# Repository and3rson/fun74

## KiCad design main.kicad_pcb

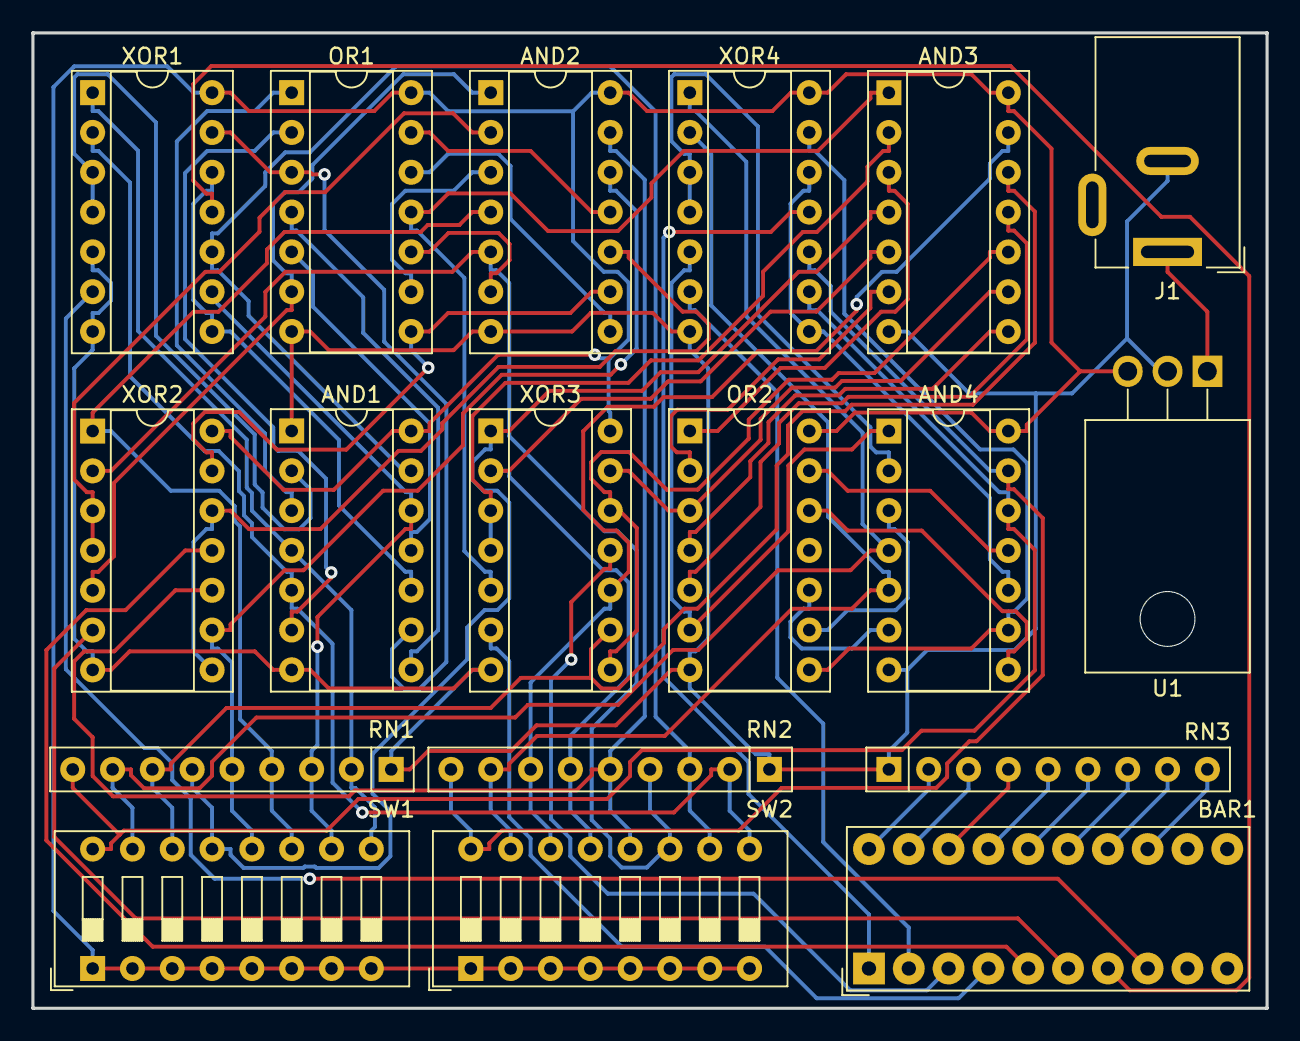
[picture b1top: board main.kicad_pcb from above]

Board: 2 copper layers, 78.7 x 62.2 mm, 18 parts (0 on the bottom side), 66 nets.

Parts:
AND1, AND2, AND3, AND4: AND; DIP-14_W7.62mm_Socket
BAR1: HDSP-4830_2; HDSP-4830
J1: Barrel_Jack_MountingPin; BarrelJack_Wuerth_6941xx301002
OR1, OR2: OR; DIP-14_W7.62mm_Socket
RN1, RN2, RN3: R_Network08; R_Array_SIP9
SW1, SW2: SW_DIP_x08; SW_DIP_SPSTx08_Slide_9.78x22.5mm_W7.62mm_P2.54mm
U1: L7805; TO-220F-3_Horizontal_TabDown
XOR1, XOR2, XOR3, XOR4: XOR; DIP-14_W7.62mm_Socket

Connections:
+5V: AND1.14 (VCC), AND2.14 (VCC), AND3.14 (VCC), AND4.14 (VCC), OR1.14 (VCC), OR2.14 (VCC), SW1.1, SW1.2, SW1.3, SW1.4, SW1.5, SW1.6, SW1.7, SW1.8, SW2.1, SW2.2, SW2.3, SW2.4, SW2.5, SW2.6, SW2.7, SW2.8, U1.3 (OUT), XOR1.14 (VCC), XOR2.14 (VCC), XOR3.14 (VCC), XOR4.14 (VCC)
/full_adder1/C_{out}: AND2.1, OR1.6, XOR2.5
/full_adder2/C_{out}: AND2.9, OR1.8, XOR2.13
/full_adder3/C_{out}: AND3.1, OR1.11, XOR3.5
/full_adder4/C_{in}: AND3.9, OR2.3, XOR3.13
/full_adder4/C_{out}: AND4.1, OR2.6, XOR4.5
/full_adder6/C_{out}: AND4.9, OR2.8, XOR4.13
/full_adder/C_{out}: AND1.9, OR1.3, XOR1.13
A_{0}: AND1.4, RN1.2 (R1), SW1.9, XOR1.1
A_{1}: AND1.12, RN1.3 (R2), SW1.10, XOR1.9
A_{2}: AND2.4, RN1.4 (R3), SW1.11, XOR2.1
A_{3}: AND2.12, RN1.5 (R4), SW1.12, XOR2.9
A_{4}: AND3.4, RN1.6 (R5), SW1.13, XOR3.1
A_{5}: AND3.12, RN1.7 (R6), SW1.14, XOR3.9
A_{6}: AND4.4, RN1.8 (R7), SW1.15, XOR4.1
A_{7}: AND4.12, RN1.9 (R8), SW1.16, XOR4.9
B_{0}: AND1.5, RN2.2 (R1), SW2.9, XOR1.2
B_{1}: AND1.13, RN2.3 (R2), SW2.10, XOR1.10
B_{2}: AND2.5, RN2.4 (R3), SW2.11, XOR2.2
B_{3}: AND2.13, RN2.5 (R4), SW2.12, XOR2.10
B_{4}: AND3.5, RN2.6 (R5), SW2.13, XOR3.2
B_{5}: AND3.13, RN2.7 (R6), SW2.14, XOR3.10
B_{6}: AND4.5, RN2.8 (R7), SW2.15, XOR4.2
B_{7}: AND4.13, RN2.9 (R8), SW2.16, XOR4.10
C_{0}: BAR1.8 (A), XOR1.6
C_{1}: BAR1.7 (A), XOR1.11
C_{2}: BAR1.6 (A), XOR2.6
C_{3}: BAR1.5 (A), XOR2.11
C_{4}: BAR1.4 (A), XOR3.6
C_{5}: BAR1.3 (A), XOR3.11
C_{6}: BAR1.2 (A), XOR4.6
C_{7}: BAR1.1 (A), XOR4.11
GND: AND1.1, AND1.7 (GND), AND2.7 (GND), AND3.7 (GND), AND4.7 (GND), J1.2, OR1.7 (GND), OR2.7 (GND), RN1.1 (common), RN2.1 (common), RN3.1 (common), U1.2 (GND), XOR1.5, XOR1.7 (GND), XOR2.7 (GND), XOR3.7 (GND), XOR4.7 (GND)
unnamed: AND1.2, XOR1.3, XOR1.4
unnamed: AND1.3, OR1.1
unnamed: AND1.6, OR1.2
unnamed: AND1.8, OR1.4
unnamed: AND1.10, XOR1.8, XOR1.12
unnamed: AND1.11, OR1.5
unnamed: AND2.2, XOR2.3, XOR2.4
unnamed: AND2.3, OR1.9
unnamed: AND2.6, OR1.10
unnamed: AND2.8, OR1.12
unnamed: AND2.10, XOR2.8, XOR2.12
unnamed: AND2.11, OR1.13
unnamed: AND3.2, XOR3.3, XOR3.4
unnamed: AND3.3, OR2.1
unnamed: AND3.6, OR2.2
unnamed: AND3.8, OR2.4
unnamed: AND3.10, XOR3.8, XOR3.12
unnamed: AND3.11, OR2.5
unnamed: AND4.2, XOR4.3, XOR4.4
unnamed: AND4.3, OR2.9
unnamed: AND4.6, OR2.10
unnamed: AND4.8, OR2.12
unnamed: AND4.10, XOR4.8, XOR4.12
unnamed: AND4.11, OR2.13
unnamed: BAR1.20 (K), RN3.2 (R1)
unnamed: BAR1.19 (K), RN3.3 (R2)
unnamed: BAR1.18 (K), RN3.4 (R3)
unnamed: BAR1.17 (K), RN3.5 (R4)
unnamed: BAR1.16 (K), RN3.6 (R5)
unnamed: BAR1.15 (K), RN3.7 (R6)
unnamed: BAR1.14 (K), RN3.8 (R7)
unnamed: BAR1.13 (K), RN3.9 (R8)
unnamed: J1.1, U1.1 (IN)

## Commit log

2023-10-12 Initial PCB
